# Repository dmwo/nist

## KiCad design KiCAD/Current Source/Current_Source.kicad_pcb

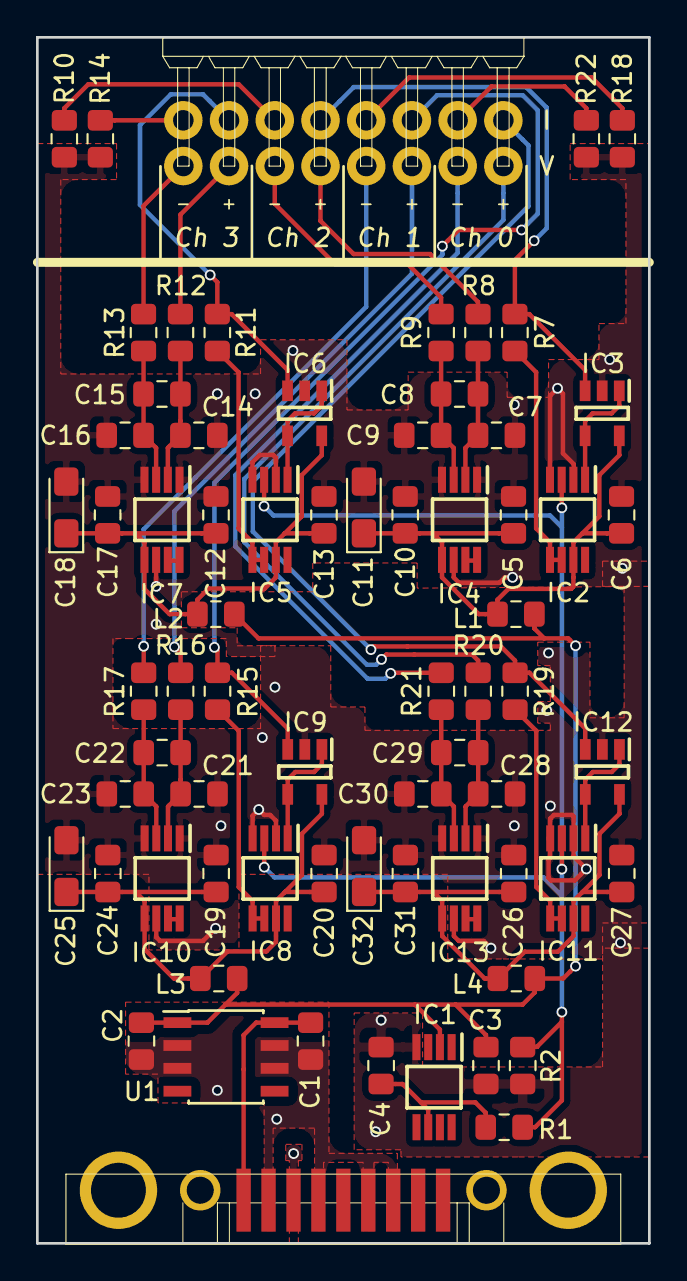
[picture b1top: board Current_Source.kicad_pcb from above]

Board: 2 copper layers, 34.0 x 67.0 mm, 70 parts (0 on the bottom side), 46 nets.

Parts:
C1: 0.33uF; C_0805_2012Metric_Pad1.15x1.40mm_HandSolder
C2: 0.01uF; C_0805_2012Metric_Pad1.15x1.40mm_HandSolder
C3, C4, C5, C6, C7, C9, C10, C12, C13, C14, C16, C17, C19, C20, C21, C23, C24, C26, C27, C28, C30, C31: 0.1uF; C_0805_2012Metric_Pad1.15x1.40mm_HandSolder
C8, C15, C22, C29: 1uF 6.3V X7R 0805; C_0805_2012Metric_Pad1.15x1.40mm_HandSolder
C11, C18, C25, C32: 10uF; CP_EIA-3216-18_Kemet-A_Pad1.58x1.35mm_HandSolder
IC1: ADR440ARMZ; SOP65P490X110-8N
IC2, IC5, IC8, IC11: AD8276ARMZ; SOP65P490X110-8N
IC3, IC6, IC9, IC12: AD8603AUJZ-R2; SOT95P280X100-5N
IC4, IC7, IC10, IC13: AD8237ARMZ; SOP65P490X110-8N
J1: DB9F; K202XHT-E9S-N
J2: 90122-0124; 90122-0128
L1, L2, L3, L4: MMZ2012Y152B; L_0805_2012Metric_Pad1.15x1.40mm_HandSolder
R1: 1050; R_0805_2012Metric_Pad1.15x1.40mm_HandSolder
R2: 1K; R_0805_2012Metric_Pad1.15x1.40mm_HandSolder
R7, R8, R9, R11, R12, R13, R15, R16, R17, R19, R20, R21: 100k; R_0805_2012Metric_Pad1.15x1.40mm_HandSolder
R10, R14, R18, R22: 10k; R_0805_2012Metric_Pad1.15x1.40mm_HandSolder
U1: LM78L05_SO8; SOIC-8_3.9x4.9mm_P1.27mm

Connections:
/1V: IC2.3, IC5.3, IC8.3, IC11.3, R1.2, R2.1
/Channel0/I+: IC12.3, J2.2, R19.2
/Channel0/I-: J2.4, R22.1
/Channel0/V+: J2.1, R20.2
/Channel0/V-: J2.3, R21.2
/Channel0/Vpower: C26.1, C27.1, C31.1, C32.1, IC11.7, IC12.5, IC13.5, L4.2
/Channel0/out: IC13.7, IC13.8
/Channel1/I+: IC9.3, J2.6, R15.2
/Channel1/I-: J2.8, R18.1
/Channel1/V+: J2.5, R16.2
/Channel1/V-: J2.7, R17.2
/Channel1/Vpower: C19.1, C20.1, C24.1, C25.1, IC8.7, IC9.5, IC10.5, L3.2
/Channel1/out: IC10.7, IC10.8
/Channel2/I+: IC3.3, J2.10, R7.2
/Channel2/I-: J2.12, R10.1
/Channel2/V+: J2.9, R8.2
/Channel2/V-: J2.11, R9.2
/Channel2/Vpower: C5.1, C6.1, C10.1, C11.1, IC2.7, IC3.5, IC4.5, L1.2
/Channel2/out: IC4.7, IC4.8
/Channel3/I+: IC6.3, J2.14, R11.2
/Channel3/I-: J2.16, R14.1
/Channel3/V+: J2.13, R12.2
/Channel3/V-: J2.15, R13.2
/Channel3/Vpower: C12.1, C13.1, C17.1, C18.1, IC5.7, IC6.5, IC7.5, L2.2
/Channel3/out: IC7.7, IC7.8
/Power: C2.1, C3.1, IC1.2, L1.1, L2.1, L3.1, L4.1, U1.1
GND: C1.2, C2.2, J1.4, J1.6, J1.7, J1.8, U1.2, U1.3, U1.6, U1.7
GNDA: C3.2, C4.2, C5.2, C6.2, C7.1, C9.2, C10.2, C11.2, C12.2, C13.2, C14.1, C16.2, C17.2, C18.2, C19.2, C20.2, C21.1, C23.2, C24.2, C25.2, C26.2, C27.2, C28.1, C30.2, C31.2, C32.2, IC1.4, IC2.2, IC2.4, IC3.2, IC4.1, IC4.4, IC4.6, IC5.2, IC5.4, IC6.2, IC7.1, IC7.4, IC7.6, IC8.2, IC8.4, IC9.2, IC10.1, IC10.4, IC10.6, IC11.2, IC11.4, IC12.2, IC13.1, IC13.4, IC13.6, J1.2, R2.2, R10.2, R14.2, R18.2, R22.2
unnamed: C1.1, J1.1, U1.8
unnamed: C4.1, IC1.6, R1.1
unnamed: C7.2, C8.1, IC4.2, R8.1
unnamed: C8.2, C9.1, IC4.3, R9.1
unnamed: C14.2, C15.1, IC7.2, R12.1
unnamed: C15.2, C16.1, IC7.3, R13.1
unnamed: C21.2, C22.1, IC10.2, R16.1
unnamed: C22.2, C23.1, IC10.3, R17.1
unnamed: C28.2, C29.1, IC13.2, R20.1
unnamed: C29.2, C30.1, IC13.3, R21.1
unnamed: IC2.1, IC3.1, IC3.4
unnamed: IC2.5, IC2.6, R7.1
unnamed: IC5.1, IC6.1, IC6.4
unnamed: IC5.5, IC5.6, R11.1
unnamed: IC8.1, IC9.1, IC9.4
unnamed: IC8.5, IC8.6, R15.1
unnamed: IC11.1, IC12.1, IC12.4
unnamed: IC11.5, IC11.6, R19.1

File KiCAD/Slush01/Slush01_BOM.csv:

Item #,Ref Des,Qty [individual part],Cost per unit,Manufacturer,Mfg part #,Description/Value,Package,Type,Notes,Website URL
1,C1,1,0.28,Yageo,CC0805JKX7R7BB334,0.33uF,0805 (2012 Metric),SMD,,https://www.digikey.com/product-detail/en/yageo/CC0805JKX7R7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
2,C2,1,0.15,Yageo,CC0805JRX7R9BB103,0.01uF,0805 (2012 Metric),SMD,,https://www.digikey.com/product-detail/en/yageo/CC0805JRX7R9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
3,"C8,C15,C22,C29",4,0.17,Yageo,CC0805KKX7R8BB105,1uF,0805 (2012 Metric),SMD,,https://www.digikey.com/product-detail/en/yageo/CC0805KKX7R8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
4,"C11,C18,C25,C32",4,0.48,AVX Corp,F930J106KAA,10uF Tantalum,1206 (3216 Metric),SMD,,https://www.digikey.com/product-detail/en/avx-corporation/F9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
5,"C3,C4,C5,C6,C7,C9,C10,C12,C13,C14,C16,C17,C19,C20,C21,C23,C24,C26,C27,C28,C30,C31,C33",23,0.087,Yageo,CC0805KRX7R9BB104,0.1uF,0805 (2012 Metric),SMD,,https://www.digikey.com/product-detail/en/yageo/CC0805KRX7R9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
6,"L1,L2,L3,L4",4,0.11,TDK Corp,MMZ2012Y152BTD25,Ferrite Bead 1.5k?,0805 (2012 Metric),SMD,,https://www.digikey.com/product-detail/en/tdk-corporation/MM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
7,R1,1,0.1,Yageo,RC0805FR-071K05L,1.05k,0805 (2012 Metric),SMD,,https://www.digikey.com/product-detail/en/yageo/RC0805FR-071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
8,R2,1,0.1,Yageo,RT0805FRE071KL,1k,0805 (2012 Metric),SMD,,https://www.digikey.com/product-detail/en/yageo/RT0805FRE071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
9,"R10,R14,R18,R22",4,0.14,Yageo,RT0805DRE0710KL,10k,0805 (2012 Metric),SMD,,https://www.digikey.com/product-detail/en/yageo/RT0805DRE071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
10,"R7,R8,R9,R11,R12,R13,R15,R16,R17,R19,R20,R21",12,0.127,Yageo,RT0805DRE07100KL,100k,0805 (2012 Metric),SMD,,https://www.digikey.com/product-detail/en/yageo/RT0805DRE071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
11,J1,1,3.98,Kycon,K202XHT-E9S-N,DB9 Serial Connector Female,K202XHT-E9S-N,SMD/THM,,https://www.digikey.com/product-detail/en/kycon-inc/K202XHT-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
12,J2,1,2.46,Molex,901220128,Connector Header Right Angle 16 pos,901220128,THM,,https://www.digikey.com/product-detail/en/molex/0901220128/W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
13,IC1,1,7.64,Analog Devices,ADR440ARMZ,V Ref IC,MSOP-8,SMD,,https://www.digikey.com/product-detail/en/analog-devices-inc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
14,IC14,1,0.69,Texas Instruments,LM78L05ACMX/NOPB,LM78L05 Linear Regulator,SOIC-8,SMD,,https://www.digikey.com/product-detail/en/texas-instruments/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
15,IC15,1,6.35,Texas Instruments,ADS1115IDGST,16-bit ADC,VSSOP-10,SMD,,https://www.digikey.com/product-detail/en/texas-instruments/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
16,"IC2,IC5,IC8,IC11",4,2.73,Analog Devices,AD8276ARMZ-RL,Differential Op Amp,MSOP-8,SMD,,https://www.digikey.com/product-detail/en/analog-devices-inc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
17,"IC3,IC6,IC9,IC12",4,2.73,Analog Devices,AD8603AUJZ-R2,Op Amp,TSOT-23-5,SMD,,https://www.digikey.com/product-detail/en/analog-devices-inc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
18,"IC4,IC7,IC10,IC13",4,2.7,Analog Devices,AD8237ARMZ,Instrumentation Amplifier,MSOP-8,SMD,,https://www.digikey.com/product-detail/en/analog-devices-inc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

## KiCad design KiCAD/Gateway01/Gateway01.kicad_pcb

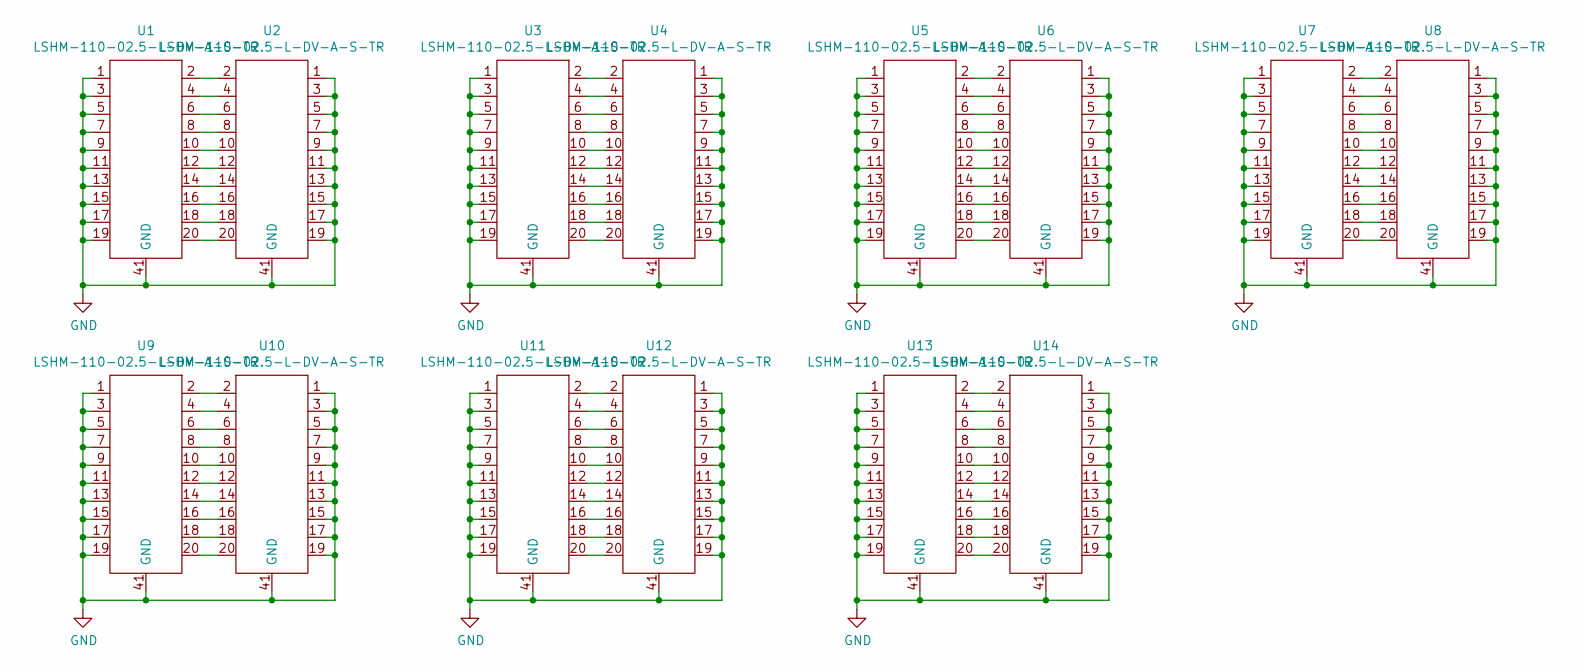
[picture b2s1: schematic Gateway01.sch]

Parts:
U1, U2, U3, U4, U5, U6, U7, U8, U9, U10, U11, U12, U13, U14: LSHM-110-02.5-L-DV-A-S-TR

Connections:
GND: U1.0, U1.1, U1.3, U1.5, U1.7, U1.9, U1.11, U1.13, U1.15, U1.17, U1.19, U1.41 (GND), U2.0, U2.1, U2.3, U2.5, U2.7, U2.9, U2.11, U2.13, U2.15, U2.17, U2.19, U2.41 (GND), U3.0, U3.1, U3.3, U3.5, U3.7, U3.9, U3.11, U3.13, U3.15, U3.17, U3.19, U3.41 (GND), U4.0, U4.1, U4.3, U4.5, U4.7, U4.9, U4.11, U4.13, U4.15, U4.17, U4.19, U4.41 (GND), U5.0, U5.1, U5.3, U5.5, U5.7, U5.9, U5.11, U5.13, U5.15, U5.17, U5.19, U5.41 (GND), U6.0, U6.1, U6.3, U6.5, U6.7, U6.9, U6.11, U6.13, U6.15, U6.17, U6.19, U6.41 (GND), U7.0, U7.1, U7.3, U7.5, U7.7, U7.9, U7.11, U7.13, U7.15, U7.17, U7.19, U7.41 (GND), U8.0, U8.1, U8.3, U8.5, U8.7, U8.9, U8.11, U8.13, U8.15, U8.17, U8.19, U8.41 (GND), U9.0, U9.1, U9.3, U9.5, U9.7, U9.9, U9.11, U9.13, U9.15, U9.17, U9.19, U9.41 (GND), U10.0, U10.1, U10.3, U10.5, U10.7, U10.9, U10.11, U10.13, U10.15, U10.17, U10.19, U10.41 (GND), U11.0, U11.1, U11.3, U11.5, U11.7, U11.9, U11.11, U11.13, U11.15, U11.17, U11.19, U11.41 (GND), U12.0, U12.1, U12.3, U12.5, U12.7, U12.9, U12.11, U12.13, U12.15, U12.17, U12.19, U12.41 (GND), U13.0, U13.1, U13.3, U13.5, U13.7, U13.9, U13.11, U13.13, U13.15, U13.17, U13.19, U13.41 (GND), U14.0, U14.1, U14.3, U14.5, U14.7, U14.9, U14.11, U14.13, U14.15, U14.17, U14.19, U14.41 (GND)
unnamed: U1.2, U2.2
unnamed: U1.4, U2.4
unnamed: U1.6, U2.6
unnamed: U1.8, U2.8
unnamed: U1.10, U2.10
unnamed: U1.12, U2.12
unnamed: U1.14, U2.14
unnamed: U1.16, U2.16
unnamed: U1.18, U2.18
unnamed: U1.20, U2.20
unnamed: U3.2, U4.2
unnamed: U3.4, U4.4
unnamed: U3.6, U4.6
unnamed: U3.8, U4.8
unnamed: U3.10, U4.10
unnamed: U3.12, U4.12
unnamed: U3.14, U4.14
unnamed: U3.16, U4.16
unnamed: U3.18, U4.18
unnamed: U3.20, U4.20
unnamed: U5.2, U6.2
unnamed: U5.4, U6.4
unnamed: U5.6, U6.6
unnamed: U5.8, U6.8
unnamed: U5.10, U6.10
unnamed: U5.12, U6.12
unnamed: U5.14, U6.14
unnamed: U5.16, U6.16
unnamed: U5.18, U6.18
unnamed: U5.20, U6.20
unnamed: U7.2, U8.2
unnamed: U7.4, U8.4
unnamed: U7.6, U8.6
unnamed: U7.8, U8.8
unnamed: U7.10, U8.10
unnamed: U7.12, U8.12
unnamed: U7.14, U8.14
unnamed: U7.16, U8.16
unnamed: U7.18, U8.18
unnamed: U7.20, U8.20
unnamed: U9.2, U10.2
unnamed: U9.4, U10.4
unnamed: U9.6, U10.6
unnamed: U9.8, U10.8
unnamed: U9.10, U10.10
unnamed: U9.12, U10.12
unnamed: U9.14, U10.14
unnamed: U9.16, U10.16
unnamed: U9.18, U10.18
unnamed: U9.20, U10.20
unnamed: U11.2, U12.2
unnamed: U11.4, U12.4
unnamed: U11.6, U12.6
unnamed: U11.8, U12.8
unnamed: U11.10, U12.10
unnamed: U11.12, U12.12
unnamed: U11.14, U12.14
unnamed: U11.16, U12.16
unnamed: U11.18, U12.18
unnamed: U11.20, U12.20
unnamed: U13.2, U14.2
unnamed: U13.4, U14.4
unnamed: U13.6, U14.6
unnamed: U13.8, U14.8
unnamed: U13.10, U14.10
unnamed: U13.12, U14.12
unnamed: U13.14, U14.14
unnamed: U13.16, U14.16
unnamed: U13.18, U14.18
unnamed: U13.20, U14.20

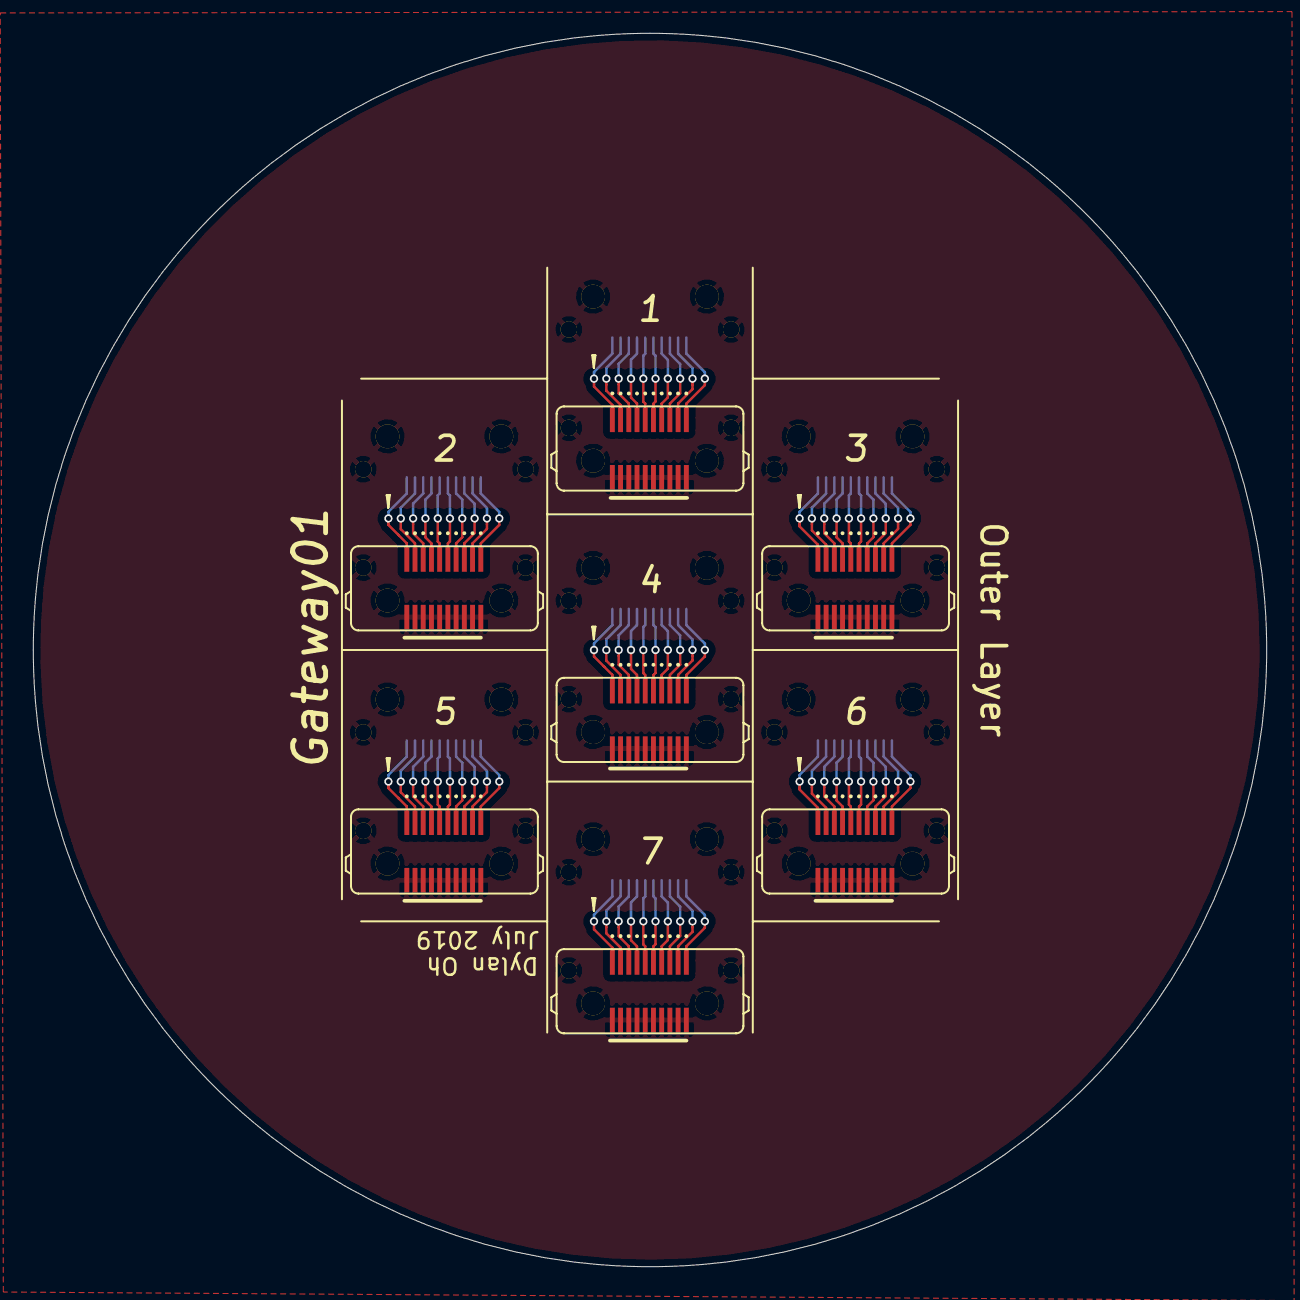
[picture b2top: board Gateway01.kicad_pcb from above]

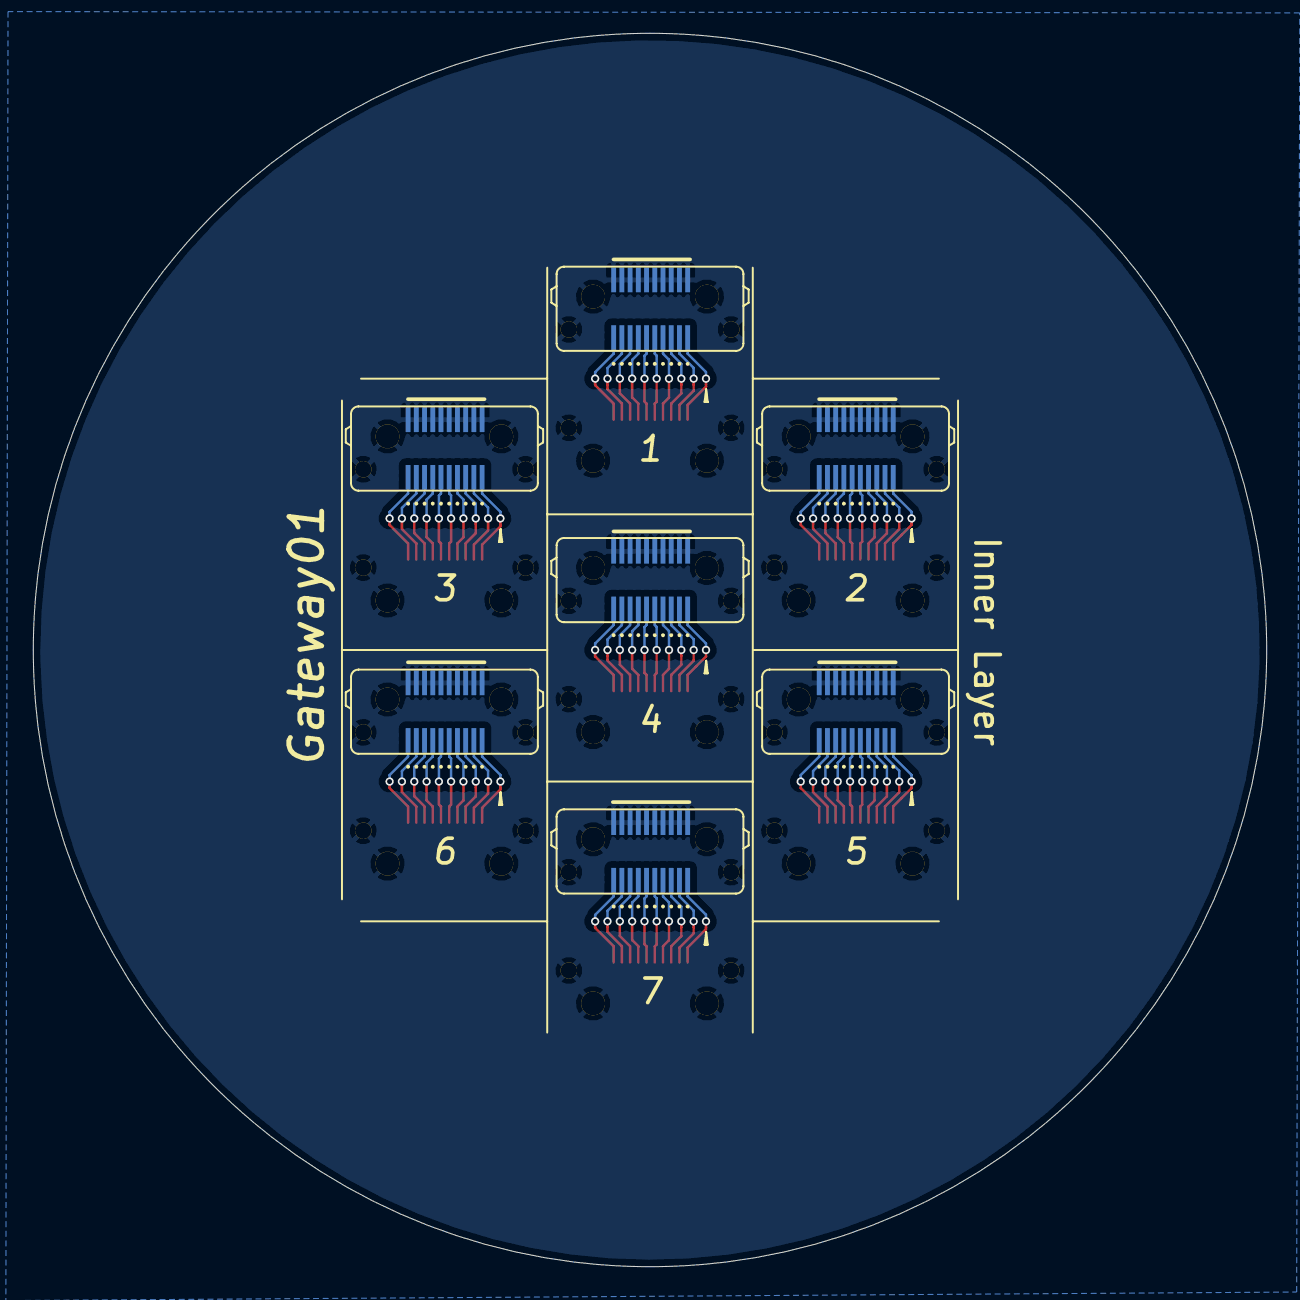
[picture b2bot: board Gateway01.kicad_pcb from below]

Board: 2 copper layers, 75.0 x 75.0 mm, 14 parts (7 on the bottom side), 71 nets.

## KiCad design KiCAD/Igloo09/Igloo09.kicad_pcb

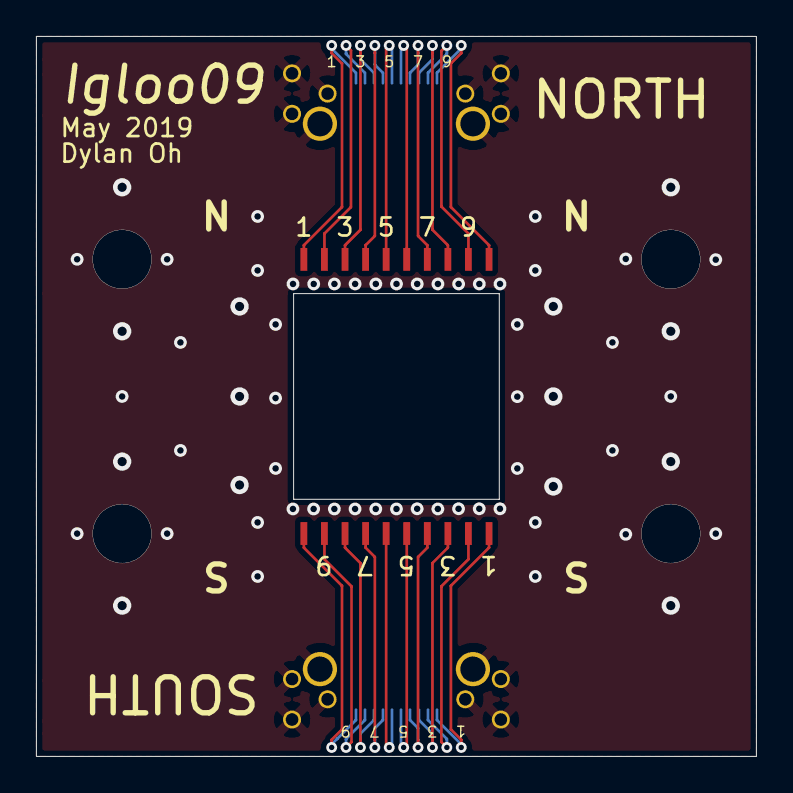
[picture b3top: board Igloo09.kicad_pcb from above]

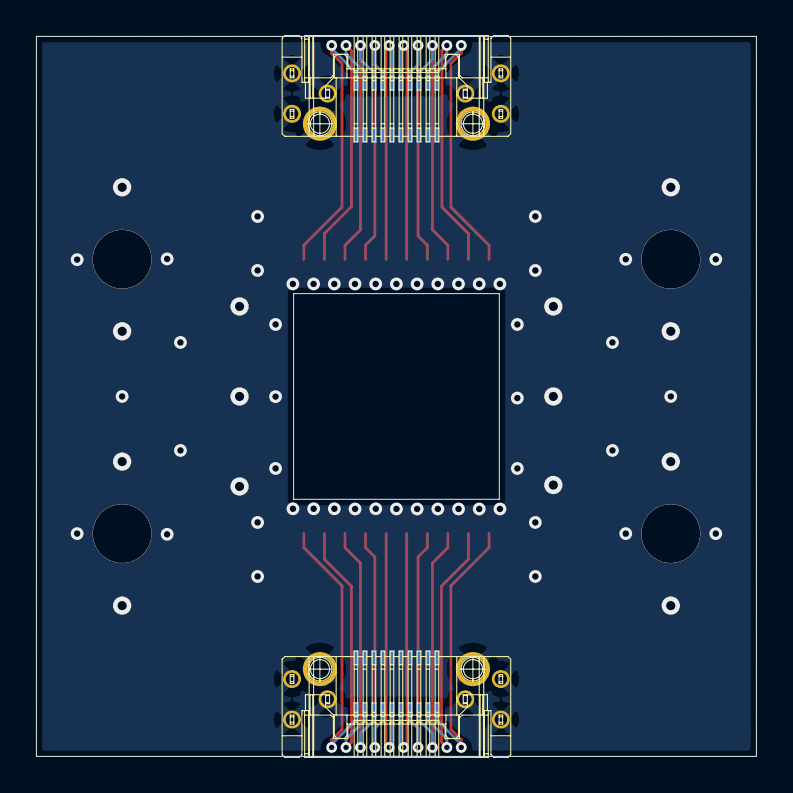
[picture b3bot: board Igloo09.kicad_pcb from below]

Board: 2 copper layers, 40.0 x 40.0 mm, 4 parts (2 on the bottom side), 21 nets.

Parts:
U1, U3: TEST_PAD
U2, U4: LSHM-110-01-L-RH-A-S-TR

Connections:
GND: U2.2, U2.4, U2.6, U2.8, U2.10, U2.12, U2.14, U2.16, U2.18, U2.20, U2.21, U4.2, U4.4, U4.6, U4.8, U4.10, U4.12, U4.14, U4.16, U4.18, U4.20, U4.21
unnamed: U1.1, U2.1
unnamed: U1.2, U2.3
unnamed: U1.3, U2.5
unnamed: U1.4, U2.7
unnamed: U1.5, U2.9
unnamed: U1.6, U2.11
unnamed: U1.7, U2.13
unnamed: U1.8, U2.15
unnamed: U1.9, U2.17
unnamed: U1.10, U2.19
unnamed: U3.1, U4.1
unnamed: U3.2, U4.3
unnamed: U3.3, U4.5
unnamed: U3.4, U4.7
unnamed: U3.5, U4.9
unnamed: U3.6, U4.11
unnamed: U3.7, U4.13
unnamed: U3.8, U4.15
unnamed: U3.9, U4.17
unnamed: U3.10, U4.19

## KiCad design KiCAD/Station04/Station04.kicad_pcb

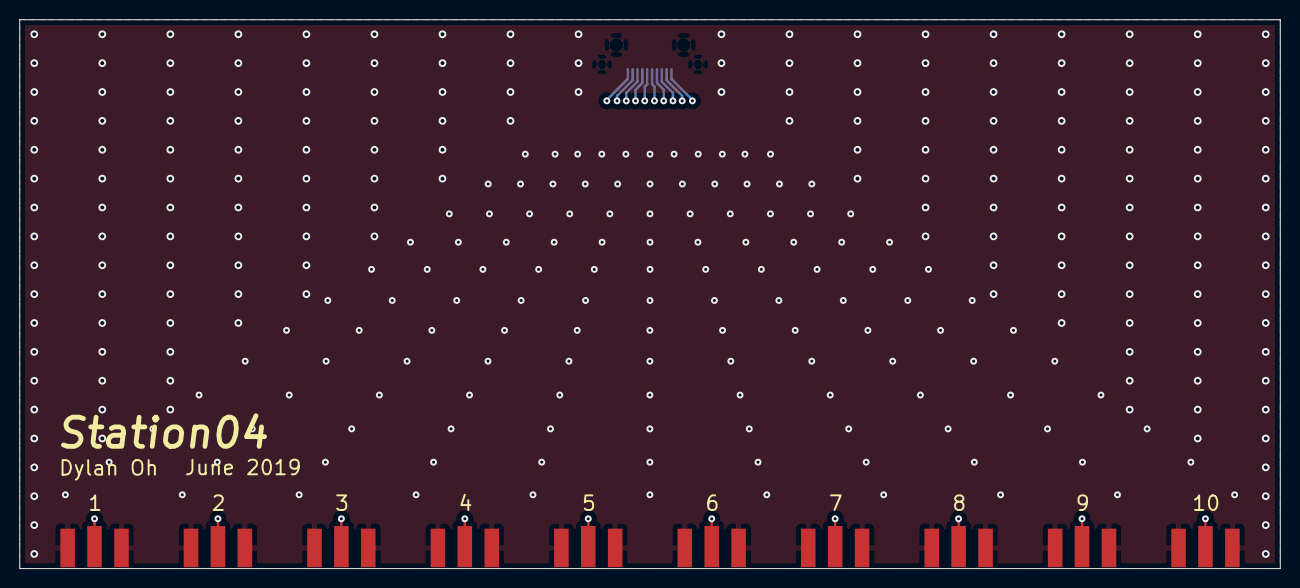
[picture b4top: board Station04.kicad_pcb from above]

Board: 4 copper layers, 129.7 x 56.5 mm, 11 parts (1 on the bottom side), 11 nets.

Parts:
U1: LSHM-110-02.5-L-DV-A-S-TR
U2, U3, U4, U5, U6, U7, U8, U9, U10, U11: CON-SMA-EDGE

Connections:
GND: U1.1, U1.3, U1.5, U1.7, U1.9, U1.11, U1.13, U1.15, U1.17, U1.19, U1.21, U2.2, U3.2, U4.2, U5.2, U6.2, U7.2, U8.2, U9.2, U10.2, U11.2
unnamed: U1.2, U2.1
unnamed: U1.4, U3.1
unnamed: U1.6, U4.1
unnamed: U1.8, U5.1
unnamed: U1.10, U6.1
unnamed: U1.12, U7.1
unnamed: U1.14, U8.1
unnamed: U1.16, U9.1
unnamed: U1.18, U10.1
unnamed: U1.20, U11.1

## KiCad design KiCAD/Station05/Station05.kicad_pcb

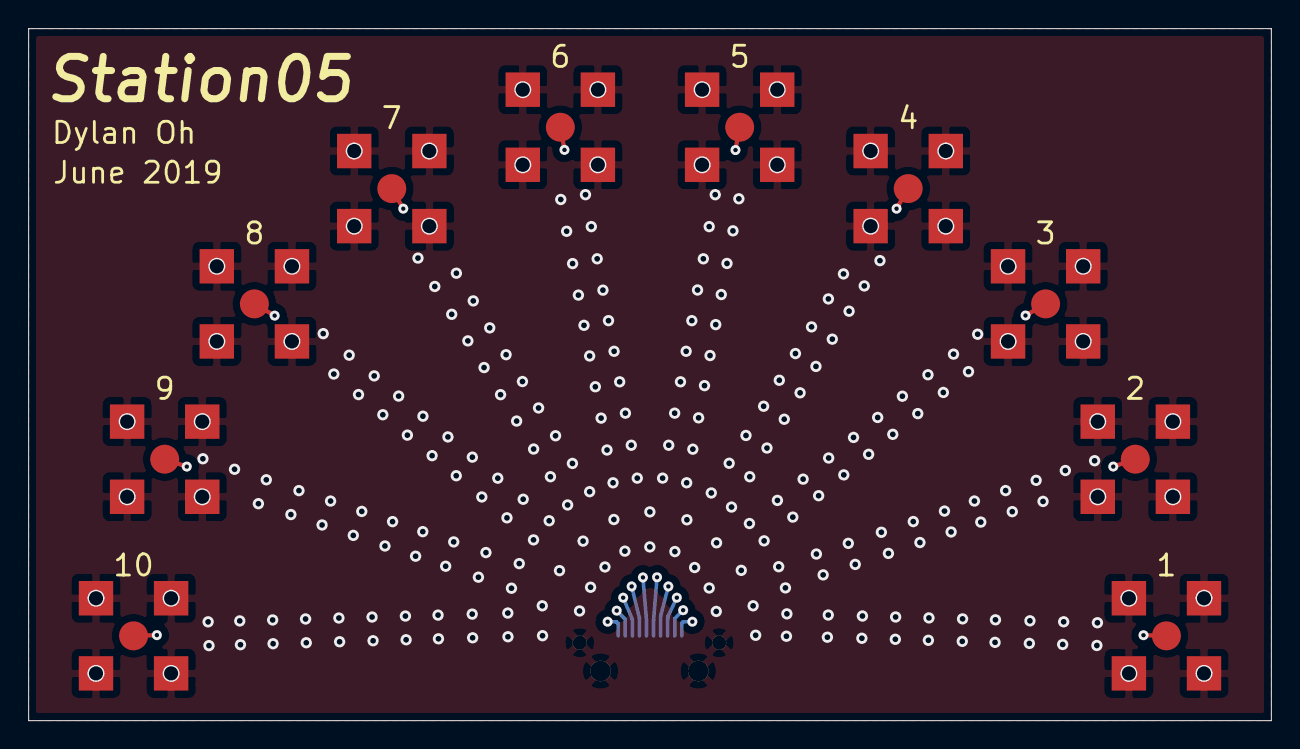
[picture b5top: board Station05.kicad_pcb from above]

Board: 4 copper layers, 88.0 x 49.0 mm, 11 parts (1 on the bottom side), 11 nets.

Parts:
U1, U2, U3, U4, U5, U6, U7, U8, U9, U10: CONSMA001-SMD-G
U11: LSHM-110-02.5-L-DV-A-S-TR

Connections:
GND: U1.2, U2.2, U3.2, U4.2, U5.2, U6.2, U7.2, U8.2, U9.2, U10.2, U11.1, U11.3, U11.5, U11.7, U11.9, U11.11, U11.13, U11.15, U11.17, U11.19, U11.21
unnamed: U1.1, U11.2
unnamed: U10.1, U11.20
unnamed: U2.1, U11.4
unnamed: U3.1, U11.6
unnamed: U4.1, U11.8
unnamed: U5.1, U11.10
unnamed: U6.1, U11.12
unnamed: U7.1, U11.14
unnamed: U8.1, U11.16
unnamed: U9.1, U11.18
